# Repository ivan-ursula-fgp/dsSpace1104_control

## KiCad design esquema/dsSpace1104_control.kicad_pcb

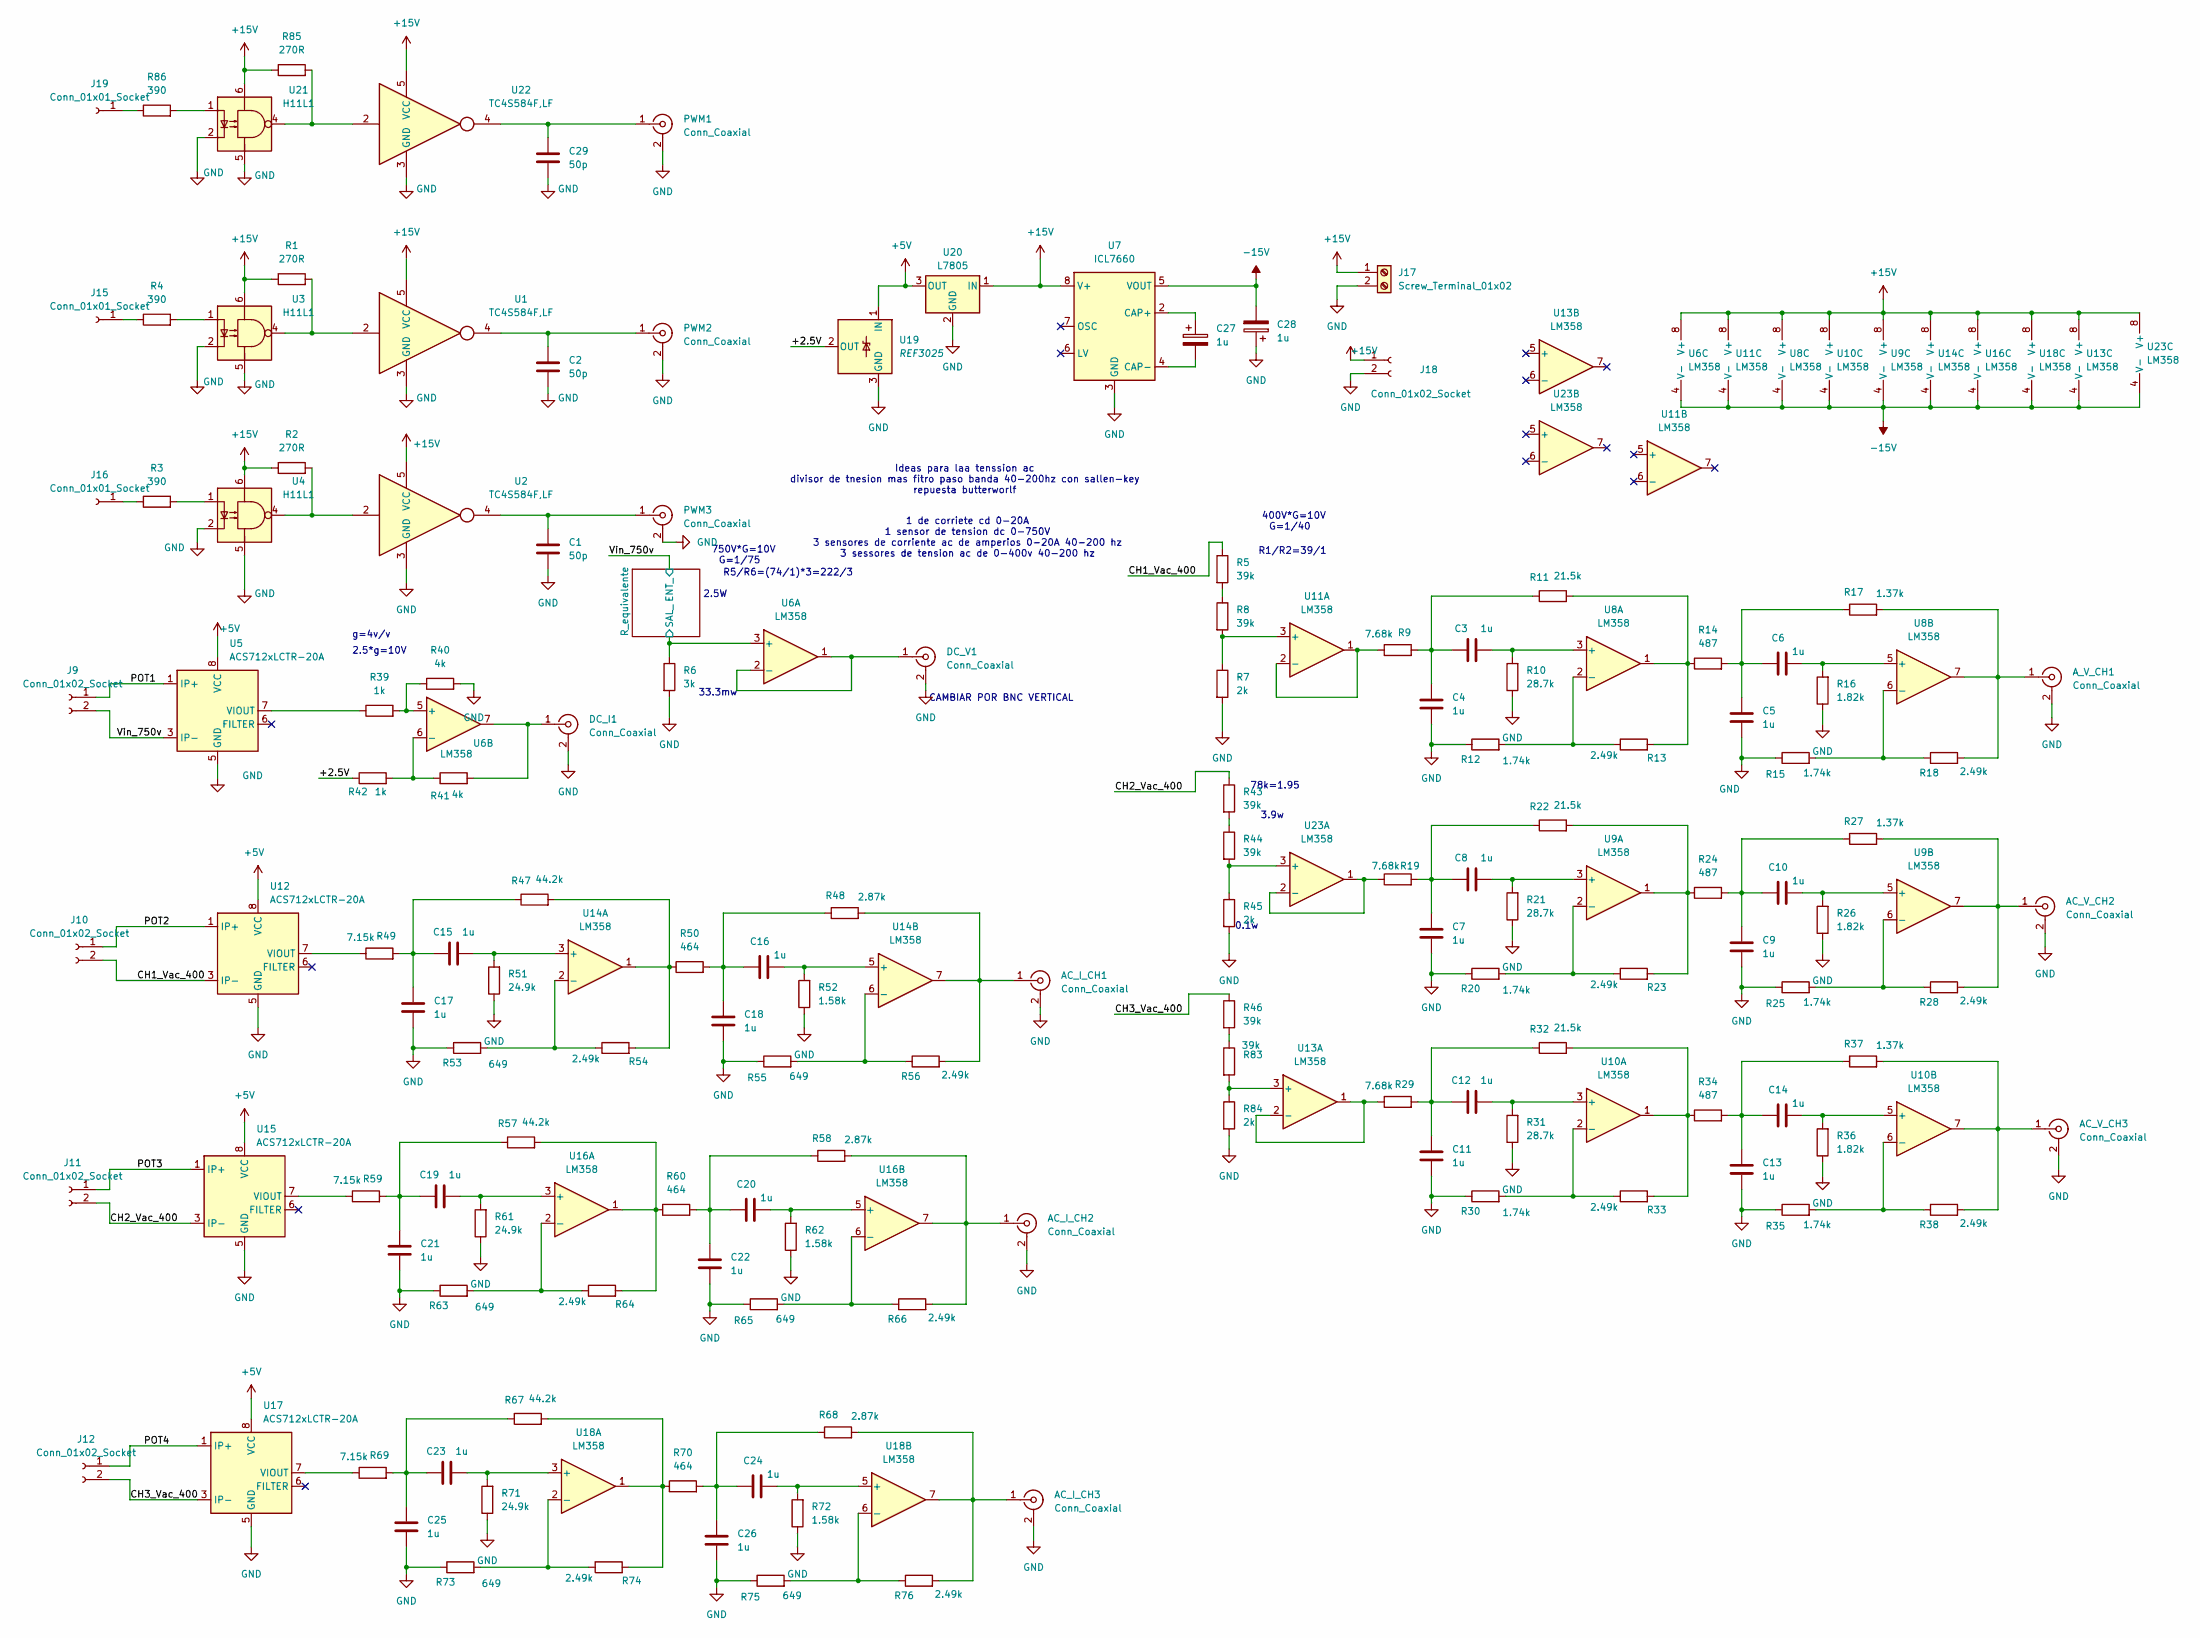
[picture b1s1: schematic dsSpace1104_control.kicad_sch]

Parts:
AC_I_CH1, AC_I_CH2, AC_I_CH3: Conn_Coaxial; SMA_Amphenol_901-144_Vertical; JLCPCB C496549
AC_V_CH2, AC_V_CH3: Conn_Coaxial; SMA_Amphenol_901-144_Vertical; JLCPCB C496549
A_V_CH1: Conn_Coaxial; SMA_Amphenol_901-144_Vertical; JLCPCB C496549
C1, C2, C29: 50p; C_0603_1608Metric_Pad1.08x0.95mm_HandSolder; JLCPCB C1672
C3, C4, C5, C6, C7, C8, C9, C10, C11, C12, C13, C14, C15, C16, C17, C18, C19, C20, C21, C22, C23, C24, C25, C26: 1u; C_0603_1608Metric_Pad1.08x0.95mm_HandSolder; JLCPCB C519560
C27, C28: 1u; CP_Elec_4x5.4; JLCPCB C3348
DC_I1: Conn_Coaxial; SMA_Amphenol_901-144_Vertical; JLCPCB C496549
DC_V1: Conn_Coaxial; SMA_Amphenol_901-144_Vertical; JLCPCB C496549
J9, J10, J11, J12, J18: Conn_01x02_Socket; Banana_Jack_2Pin
J15, J16, J19: Conn_01x01_Socket; PinHeader_1x01_P2.54mm_Vertical
J17: Screw_Terminal_01x02; TerminalBlock_MetzConnect_Type011_RT05502HBLC_1x02_P5.00mm_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
PWM1, PWM2, PWM3: Conn_Coaxial; SMA_Amphenol_901-144_Vertical; JLCPCB C496549
R1, R2, R85: 270R; R_0603_1608Metric_Pad0.98x0.95mm_HandSolder; JLCPCB C22966
R3, R4, R86: 390; R_0805_2012Metric_Pad1.20x1.40mm_HandSolder; JLCPCB C17655
R5, R8, R43, R44, R46, R83: 39k; R_2512_6332Metric_Pad1.40x3.35mm_HandSolder; JLCPCB C7209412
R6: 3k; R_0805_2012Metric_Pad1.20x1.40mm_HandSolder; JLCPCB C17661
R7, R45, R84: 2k; R_1206_3216Metric_Pad1.30x1.75mm_HandSolder; JLCPCB C17944
R9, R19, R29: 7.68k; R_0603_1608Metric_Pad0.98x0.95mm_HandSolder; JLCPCB C23102
R10, R21, R31: 28.7k; R_0603_1608Metric_Pad0.98x0.95mm_HandSolder; JLCPCB C22928
R11, R22, R32: 21.5k; R_0603_1608Metric_Pad0.98x0.95mm_HandSolder; JLCPCB C22911
R12, R15, R20, R25, R30, R35: 1.74k; R_0603_1608Metric_Pad0.98x0.95mm_HandSolder; JLCPCB C22848
R13, R18, R23, R28, R33, R38, R54, R56, R64, R66, R74, R76: 2.49k; R_0603_1608Metric_Pad0.98x0.95mm_HandSolder; JLCPCB C22908
R14, R24, R34: 487; R_0603_1608Metric_Pad0.98x0.95mm_HandSolder; JLCPCB C23064
R16, R26, R36: 1.82k; R_0603_1608Metric_Pad0.98x0.95mm_HandSolder; JLCPCB C25958
R17, R27, R37: 1.37k; R_1206_3216Metric_Pad1.30x1.75mm_HandSolder; JLCPCB C204642
R39, R42: 1k; R_0805_2012Metric_Pad1.20x1.40mm_HandSolder; JLCPCB C17513
R40, R41: 4k; R_0603_1608Metric_Pad0.98x0.95mm_HandSolder; JLCPCB C23040
R47, R57, R67: 44.2k; R_0603_1608Metric_Pad0.98x0.95mm_HandSolder; JLCPCB C23056
R48, R58, R68: 2.87k; R_0603_1608Metric_Pad0.98x0.95mm_HandSolder; JLCPCB C22907
R49, R59, R69: 7.15k; R_0603_1608Metric_Pad0.98x0.95mm_HandSolder; JLCPCB 0603
R50, R60, R70: 464; R_0603_1608Metric_Pad0.98x0.95mm_HandSolder; JLCPCB C23060
R51, R61, R71: 24.9k; R_0603_1608Metric_Pad0.98x0.95mm_HandSolder; JLCPCB C25962
R52, R62, R72: 1.58k; R_0603_1608Metric_Pad0.98x0.95mm_HandSolder; JLCPCB C22768
R53, R55, R63, R65, R73, R75: 649; R_0805_2012Metric_Pad1.20x1.40mm_HandSolder; JLCPCB C17790
U1, U2, U22: TC4S584F,LF; SOT-23-5; JLCPCB C4153812
U3, U4, U21: H11L1; DIP-6_W8.89mm_SMDSocket_LongPads; JLCPCB C78589
U5, U12, U15, U17: ACS712xLCTR-20A; SOIC-8_3.9x4.9mm_P1.27mm; JLCPCB C10681
U6, U8, U9, U10, U11, U13, U14, U16, U18, U23: LM358; SOIC-8_3.9x4.9mm_P1.27mm; JLCPCB C7950
U7: ICL7660; SOIC-8_3.9x4.9mm_P1.27mm; JLCPCB C28595
U19: REF3025; SOT-23; JLCPCB C11334
U20: L7805; TO-252-2; JLCPCB C55509

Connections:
+5V: U5.8 (VCC), U12.8 (VCC), U15.8 (VCC), U17.8 (VCC), U19.1 (IN), U20.3 (OUT)
+15V: J17.1, J18.1, R1.1, R2.1, R85.1, U1.5 (VCC), U2.5 (VCC), U3.6, U4.6, U6.8 (V+), U7.8 (V+), U8.8 (V+), U9.8 (V+), U10.8 (V+), U11.8 (V+), U13.8 (V+), U14.8 (V+), U16.8 (V+), U18.8 (V+), U20.1 (IN), U21.6, U22.5 (VCC), U23.8 (V+)
-15V: C28.2, U6.4 (V-), U7.5 (VOUT), U8.4 (V-), U9.4 (V-), U10.4 (V-), U11.4 (V-), U13.4 (V-), U14.4 (V-), U16.4 (V-), U18.4 (V-), U23.4 (V-)
/+2.5V: R42.1, U19.2 (OUT)
/CH1_Vac_400: J10.2, R5.1, U12.3 (IP-), U12.4 (IP-)
/CH2_Vac_400: J11.2, R43.1, U15.3 (IP-), U15.4 (IP-)
/CH3_Vac_400: J12.2, R46.1, U17.3 (IP-), U17.4 (IP-)
/POT1: J9.1, U5.1 (IP+), U5.2 (IP+)
/POT2: J10.1, U12.1 (IP+), U12.2 (IP+)
/POT3: J11.1, U15.1 (IP+), U15.2 (IP+)
/POT4: J12.1, U17.1 (IP+), U17.2 (IP+)
/R_equivalente/SAL_: R6.1, U6.3 (+); also elsewhere on the board
/Vin_750v: J9.2, U5.3 (IP-), U5.4 (IP-); also elsewhere on the board
GND: AC_I_CH1.2 (Ext), AC_I_CH2.2 (Ext), AC_I_CH3.2 (Ext), AC_V_CH2.2 (Ext), AC_V_CH3.2 (Ext), A_V_CH1.2 (Ext), C1.2, C2.2, C4.1, C5.1, C7.1, C9.1, C11.1, C13.1, C17.1, C18.1, C21.1, C22.1, C25.1, C26.1, C28.1, C29.2, DC_I1.2 (Ext), DC_V1.2 (Ext), J17.2, J18.2, PWM1.2 (Ext), PWM2.2 (Ext), PWM3.2 (Ext), R6.2, R7.2, R10.1, R12.1, R15.1, R16.1, R20.1, R21.1, R25.1, R26.1, R30.1, R31.1, R35.1, R36.1, R40.2, R45.2, R51.1, R52.1, R53.1, R55.1, R61.1, R62.1, R63.1, R65.1, R71.1, R72.1, R73.1, R75.1, R84.2, U1.3 (GND), U2.3 (GND), U3.2, U3.5, U4.2, U4.5, U5.5 (GND), U7.3 (GND), U12.5 (GND), U15.5 (GND), U17.5 (GND), U19.3 (GND), U20.2 (GND), U21.2, U21.5, U22.3 (GND)
unnamed: AC_I_CH1.1 (In), R48.2, R56.2, U14.7
unnamed: AC_I_CH2.1 (In), R58.2, R66.2, U16.7
unnamed: AC_I_CH3.1 (In), R68.2, R76.2, U18.7
unnamed: AC_V_CH2.1 (In), R27.2, R28.2, U9.7
unnamed: AC_V_CH3.1 (In), R37.2, R38.2, U10.7
unnamed: A_V_CH1.1 (In), R17.2, R18.2, U8.7
unnamed: C3.1, C4.2, R9.2, R11.1
unnamed: C5.2, C6.1, R14.2, R17.1
unnamed: C7.2, C8.1, R19.2, R22.1
unnamed: C9.2, C10.1, R24.2, R27.1
unnamed: C11.2, C12.1, R29.2, R32.1
unnamed: C13.2, C14.1, R34.2, R37.1
unnamed: C15.1, C17.2, R47.1, R49.2
unnamed: C16.1, C18.2, R48.1, R50.2
unnamed: C19.1, C21.2, R57.1, R59.2
unnamed: C20.1, C22.2, R58.1, R60.2
unnamed: C23.1, C25.2, R67.1, R69.2
unnamed: C24.1, C26.2, R68.1, R70.2
unnamed: DC_I1.1 (In), R41.2, U6.7
unnamed: DC_V1.1 (In), U6.1, U6.2 (-)
unnamed: J15.1, R4.1
unnamed: J16.1, R3.1
unnamed: J19.1, R86.1
unnamed: C29.1, PWM1.1 (In), U22.4
unnamed: C2.1, PWM2.1 (In), U1.4
unnamed: C1.1, PWM3.1 (In), U2.4
unnamed: R1.2, U1.2, U3.4
unnamed: R2.2, U2.2, U4.4
unnamed: R3.2, U4.1
unnamed: R4.2, U3.1
unnamed: R5.2, R8.1
unnamed: R11.2, R13.2, R14.1, U8.1
unnamed: R22.2, R23.2, R24.1, U9.1
unnamed: R32.2, R33.2, R34.1, U10.1
unnamed: R43.2, R44.1
unnamed: R46.2, R83.1
unnamed: R47.2, R50.1, R54.2, U14.1
unnamed: R57.2, R60.1, R64.2, U16.1
unnamed: R67.2, R70.1, R74.2, U18.1
unnamed: R85.2, U21.4, U22.2
unnamed: R86.2, U21.1
unnamed: R39.1, U5.7 (VIOUT)
unnamed: R39.2, R40.1, U6.5 (+)
unnamed: R41.1, R42.2, U6.6 (-)
unnamed: C27.1, U7.2 (CAP+)
unnamed: C27.2, U7.4 (CAP-)
unnamed: C3.2, R10.2, U8.3 (+)
unnamed: R12.2, R13.1, U8.2 (-)
unnamed: C6.2, R16.2, U8.5 (+)
unnamed: R15.2, R18.1, U8.6 (-)
unnamed: C8.2, R21.2, U9.3 (+)
unnamed: R20.2, R23.1, U9.2 (-)
unnamed: C10.2, R26.2, U9.5 (+)
unnamed: R25.2, R28.1, U9.6 (-)
unnamed: C12.2, R31.2, U10.3 (+)
unnamed: R30.2, R33.1, U10.2 (-)
unnamed: C14.2, R36.2, U10.5 (+)
unnamed: R35.2, R38.1, U10.6 (-)
unnamed: R7.1, R8.2, U11.3 (+)
unnamed: R9.1, U11.1, U11.2 (-)
unnamed: R49.1, U12.7 (VIOUT)
unnamed: R83.2, R84.1, U13.3 (+)
unnamed: R29.1, U13.1, U13.2 (-)
unnamed: C15.2, R51.2, U14.3 (+)
unnamed: R53.2, R54.1, U14.2 (-)
unnamed: C16.2, R52.2, U14.5 (+)
unnamed: R55.2, R56.1, U14.6 (-)
unnamed: R59.1, U15.7 (VIOUT)
unnamed: C19.2, R61.2, U16.3 (+)
unnamed: R63.2, R64.1, U16.2 (-)
unnamed: C20.2, R62.2, U16.5 (+)
unnamed: R65.2, R66.1, U16.6 (-)
unnamed: R69.1, U17.7 (VIOUT)
unnamed: C23.2, R71.2, U18.3 (+)
unnamed: R73.2, R74.1, U18.2 (-)
unnamed: C24.2, R72.2, U18.5 (+)
unnamed: R75.2, R76.1, U18.6 (-)
unnamed: R44.2, R45.1, U23.3 (+)
unnamed: R19.1, U23.1, U23.2 (-)

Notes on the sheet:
2.5*g=10V
R5/R6=(74/1)*3=222/3
Ideas para laa tenssion ac divisor de tnesion mas fitro paso banda 40-200hz con sallen-key repuesta butterworlf
400V*G=10V
750V*G=10V
2.5W
g=4v/v
78k=1.95
33.3mw
1 de corriete cd 0-20A 1 sensor de tension dc 0-750V 3 sensores de corriente ac de amperios 0-20A 40-200 hz 3 sessores de tension ac de 0-400v 40-200 hz
3.9w
R1/R2=39/1
CAMBIAR POR BNC VERTICAL
0.1w
G=1/75
G=1/40

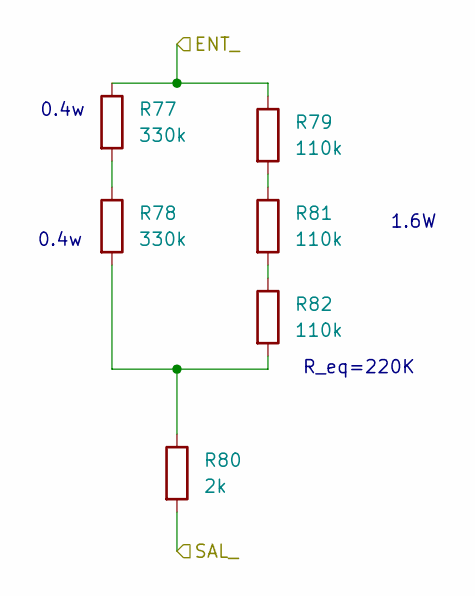
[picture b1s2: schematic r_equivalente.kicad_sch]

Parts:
R77, R78: 330k; R_2512_6332Metric_Pad1.40x3.35mm_HandSolder; JLCPCB 2512
R79, R81, R82: 110k; R_2512_6332Metric_Pad1.40x3.35mm_HandSolder; JLCPCB C30708
R80: 2k; R_1206_3216Metric_Pad1.30x1.75mm_HandSolder; JLCPCB C17944

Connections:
/R_equivalente/SAL_: R80.2; also elsewhere on the board
/Vin_750v: R77.1, R79.1; also elsewhere on the board
unnamed: R77.2, R78.1
unnamed: R78.2, R80.1, R82.2
unnamed: R79.2, R81.1
unnamed: R81.2, R82.1

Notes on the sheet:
1.6W
0.4w
R_eq=220K

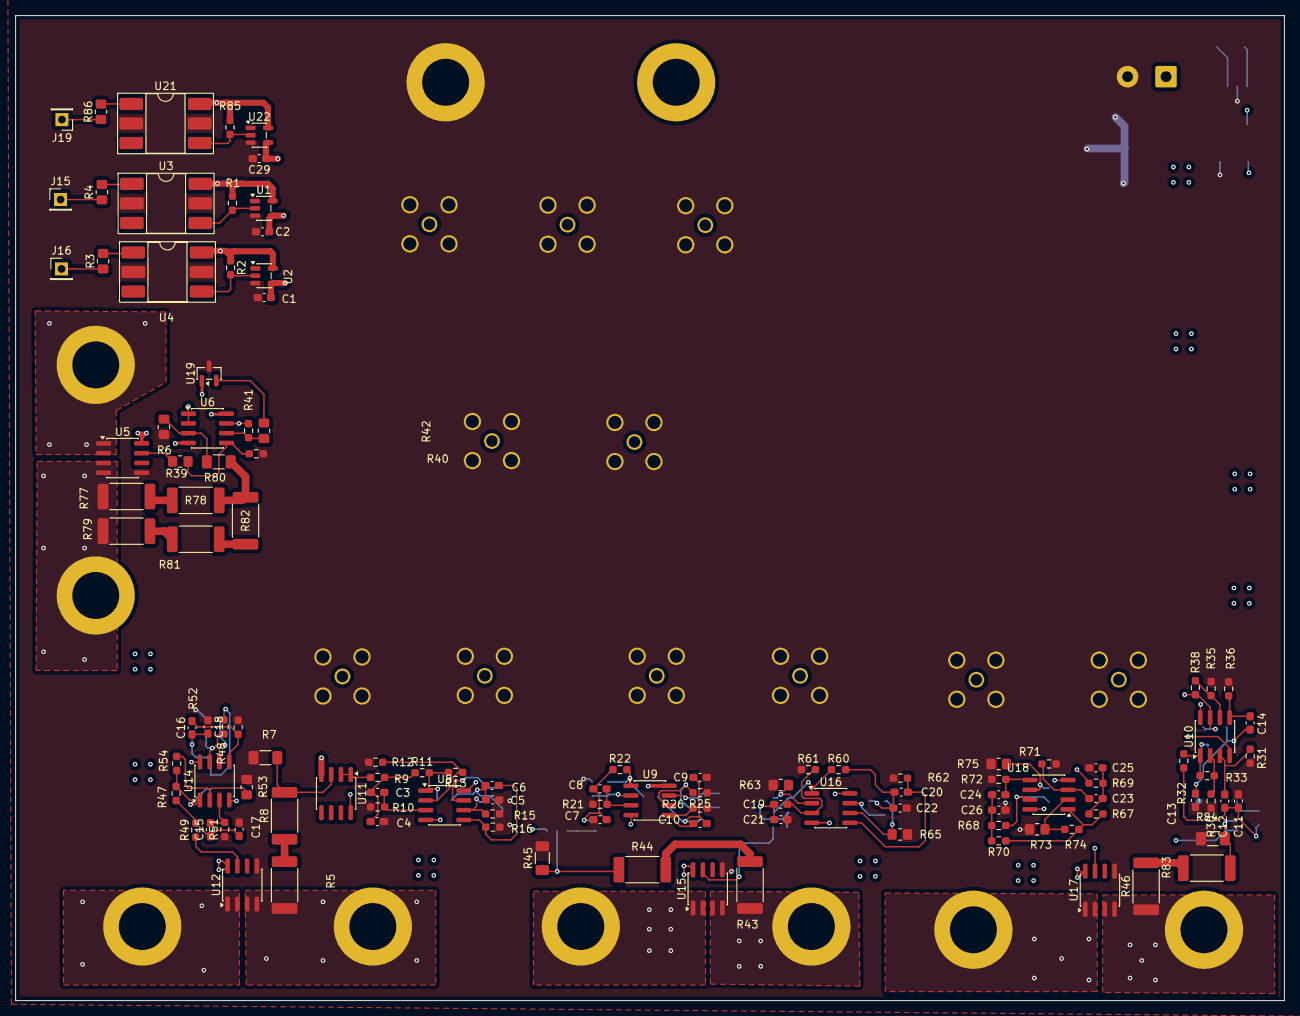
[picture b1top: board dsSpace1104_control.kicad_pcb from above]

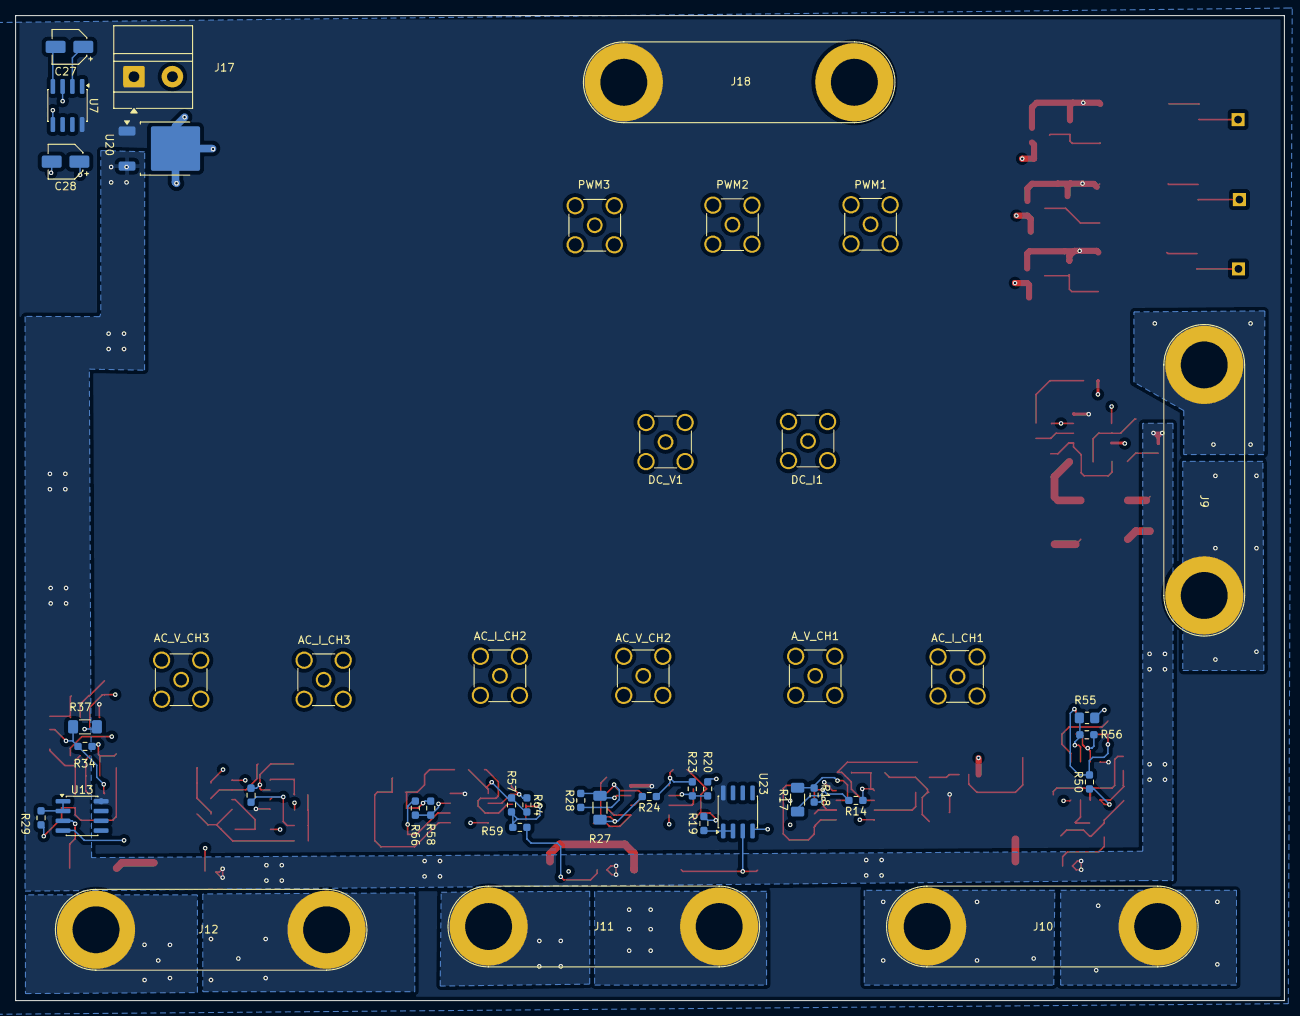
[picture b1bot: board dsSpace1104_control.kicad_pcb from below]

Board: 4 copper layers, 164.9 x 128.0 mm, 158 parts (44 on the bottom side), 97 nets.

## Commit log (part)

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2026-06-17 creo esquema kicad v9
2026-06-18 señal pwm terminada
